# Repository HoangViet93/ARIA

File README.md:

# SRS Studio

Quản lý System / Component Requirements cho automotive — kiểu Codebeamer nhưng
gọn, chạy offline, và **lưu dữ liệu thẳng trong LaTeX** để versioning bằng git.

- Cây item lồng nhau, bảy loại: **Information / Function / Design / DVP /
  Calibration / Interface / Component**
- Mã item bền vững `BCM-0007`, không bao giờ tái sử dụng
- Rich text đầy đủ: bảng, ảnh, link ngoài, link nội bộ tới item, công thức
- Sáu góc nhìn: Tài liệu · Bảng item · **Truy vết dạng sơ đồ** · **UI/UX** ·
  **Component** · LaTeX
- Tín hiệu và biến hiệu chuẩn dạng **enum**: danh sách giá trị, mặc định chọn
  ngay trong danh sách nên không lệch được
- **Sticker ảnh hưởng UI/UX** trên Function/Design, kèm Setting người dùng và
  Cảnh báo — gom thành một bảng để gửi team HMI
- **Component** (ECU/module) là một item riêng, hiển thị bảng gộp và mention
  được bằng `@` (3 tab riêng: Component/Calibration/Interface) — tab Component
  lọc mọi Design nhắc tới nó, trích đúng đoạn văn/bullet/hàng bảng chứa mention
  chứ không phải cả item. ECU gửi/nhận của Interface cũng mention được, kèm
  trường Lớp vật lý (CAN/LIN/Ethernet/Hardwired)
- Tìm kiếm TOC theo **toàn bộ nội dung** (không chỉ tiêu đề/mã), lọc thêm theo
  loại item
- Mỗi lần lưu có thay đổi đều tự chụp một bản vào `.history/`, khôi phục bằng nút **Bản lưu**
- **Git tích hợp sẵn**: mỗi project là một repo từ lúc tạo. Bảng lịch sử bên phải
  (`Ctrl+H`), xem lại bản cũ ở chế độ chỉ đọc, baseline bằng tag, khôi phục cả
  tài liệu hoặc từng item — và **so sánh hai phiên bản ở mức item**, không phải mức dòng
- **Workspace nhiều sách**: một repo git cho cả một chương trình xe (vd.
  `VF9-SRS`), gồm nhiều sách (mỗi sách vẫn là một `data.tex` như trước). Mở
  workspace hiện thanh chuyển sách ở đầu màn hình; bảng Lịch sử chỉ lọc theo
  đúng sách đang mở (`git log -- <sách>/data.tex`), không lẫn sách khác.
  **Xuất Excel** quét Function của mọi sách trong workspace ra một file. Nhánh
  git (tạo/merge trên Gerrit, ngoài app) có thể **checkout** thẳng trong app —
  chuyển cả workspace sang trạng thái của nhánh đó.
- Xuất PDF qua XeLaTeX (tiếng Việt có dấu, mục lục, bookmark)
- Zoom khung tài liệu (`Ctrl` + con lăn), tối đa là mức vừa bề rộng trang
- Chịu được sách dài: 288 trang / 1 150 item vẫn cuộn 60 fps — xem
  `docs/PERFORMANCE.md`
- **aria-sim** (`sim/`): mô phỏng sơ đồ khối kiểu Simulink cho MIL theo yêu
  cầu và desktop calibration — monitor yêu cầu chạy trên cả kết quả mô phỏng
  lẫn log xe, nhận dạng tham số plant từ log, nhập/xuất DCM, nhập thẳng từ
  sách ARIA. Xem `sim/README.md`; chạy `npm run sim`.

Đọc `docs/FEATURES.md` (phân tích + feature requirement), `docs/DESIGN.md`
(thiết kế chi tiết) và `docs/PERFORMANCE.md` (đo và tối ưu hiệu năng).

## Yêu cầu

- Node.js >= 18
- XeLaTeX (chỉ cần khi Xuất/Xem trước PDF) với các gói: `fontspec geometry
  array longtable booktabs tabularx graphicx xcolor colortbl enumitem needspace
  titlesec fancyhdr ulem hyperref tikz`
- Font DejaVu Serif / Sans / Sans Mono

## Chạy

```bash
npm install
npm start
```

Nếu Node hoặc TeX Live nằm trong thư mục home (không cài hệ thống), dùng:

```bash
./run.sh
```

## Đóng gói bản Windows

```bash
npm run dist:win
```

Ra `dist/ARIA-<version>-win-portable/` (và file `.zip` tương ứng) — một
**folder**, không phải file `.exe` đơn — kèm sẵn TeX Live rút gọn
(`resources/texlive-win`) nên máy Windows đích không cần cài TeX Live/MiKTeX
riêng để xuất PDF. Người dùng chỉ cần giải nén rồi bấm đúp `Start-ARIA.bat`.

**Vì sao không đóng gói thành 1 file `.exe`:** đã thử (electron-builder, cả
dạng NSIS lẫn dạng đổi tên `electron.exe` trần) — Windows **Smart App
Control** chặn cứng (không có nút "Run anyway") bất kỳ file `.exe` mới, chưa
ký số, chưa có danh tiếng nào, và **mỗi lần build lại app là ra một file khác
hoàn toàn** (icon/version resource nhúng khác, nội dung `app.asar` khác) nên
không bao giờ "tích lũy" được danh tiếng. `Start-ARIA.bat` là văn bản thuần
(không phải PE binary) và chỉ gọi thẳng `node_modules/electron/dist/electron.exe`
— bản `electron.exe` **gốc, chưa chỉnh sửa gì**, giống hệt bản mà rất nhiều
app Electron khác dùng, nên không phải là "một binary mới lạ" theo cách
Smart App Control đánh giá. Không có cách đóng gói `.exe` đơn nào né được vấn
đề này nếu không mua chứng chỉ code-signing thật hoặc tắt hẳn Smart App
Control trên máy đích (tắt là một chiều, không bật lại được nếu không cài lại
Windows).

`scripts/build-portable-win.js` tự tải riêng một bản Electron Windows-x64 (ép
qua `npm_config_platform=win32 npm_config_arch=x64`, khác với `node_modules`
Linux/macOS bạn đang dùng để phát triển) và chỉ mang theo đúng ba gói npm mà
`main.js`/`lib/` thực sự `require()` lúc chạy (`electron`, `isomorphic-git`,
`exceljs`) — không kèm `esbuild` hay các gói dev khác.

## Kiểm thử

```bash
npm test            # 95 ca: model, checker, diff, git, rich text, biên dịch LaTeX thật
npm run test:ui     # 62 ca trên Electron thật (CRUD, 4 tab, lưu, bản lưu)
npm run test:editor # 59 ca bấm từng nút của editor rồi so LaTeX sinh ra
npm run test:git    # 52 ca cho luồng git: commit, xem bản cũ, so sánh, baseline, khôi phục
npm run test:workspace # 17 ca workspace nhiều sách: chuyển sách, lịch sử lọc theo sách, checkout, xuất Excel
npm run test:all    # tất cả — 285 khẳng định
npm run check       # lint data.tex của các project mẫu
```

## Ba project mẫu

| Project | Nội dung |
|---|---|
| `projects/BCM-Door-Lock` | 10 item, 3 cấp — ví dụ tối giản để xem cấu trúc |
| `projects/EPB-Park-Brake` | 22 item, 4 cấp — Electric Park Brake, dùng hết mọi tính năng: ảnh sơ đồ, 5 bảng, công thức, link nội bộ giữa các item, đủ 5 mức ASIL, và một Function cố ý chưa có Design để tab Truy vết có việc báo. **Có sẵn 15 commit và 2 baseline** (`rev-A`, `rev-B`) trải từ tháng 6 đến tháng 9 để thử bảng Lịch sử |
| `projects/VF9-SRS` | **Workspace 4 sách** (EPB, BCM, ADAS, HVAC) trong 1 repo — ví dụ cho tính năng multi-book. Mỗi sách có lịch sử riêng đã seed sẵn; có thêm nhánh `review/epb-emergency-brake` diverge riêng trên sách EPB để thử **checkout**. Sinh lại bằng `npm run sample:workspace -- --force` |

`projects/BCM-Door-Lock` cố ý **chưa** có git — để thử luồng "Khởi tạo git" một nút.

Lịch sử của EPB dựng bằng `npm run seed-history` (thêm `--force` để dựng lại).
Script giữ nguyên từng byte `data.tex` hiện có, nên chỉnh sửa tay không bị mất.
Ba mốc đáng xem khi so sánh:

| So sánh | Thấy gì |
|---|---|
| `rev-A` → `rev-B` | 11 item mới, 3 chuyển chỗ, ASIL tăng C→D (cảnh báo vàng) |
| "Định nghĩa khung CAN" → "Rút gọn kiểm chứng cho DEB" | bỏ Simulation và Demonstration — **cảnh báo đỏ** |
| "Thêm phanh khẩn cấp" → "Siết ASIL" | ASIL C→D kèm bổ sung Review |

Sinh lại bằng `npm run sample` / `node scripts/make-epb-sample.js`
(ảnh sơ đồ: `npx electron scripts/make-diagram.js`).

## Cấu trúc một project

```
MyProject/
  data.tex        ← TOÀN BỘ dữ liệu. Sửa tay được, git diff có nghĩa.
  images/         ← ảnh đính kèm
  .git/           ← repo chuẩn; git CLI và mọi GUI git đều đọc được
  .gitignore      ← app tạo
  .history/       ← bản lưu tự động trước mỗi lần ghi đè (giữ 30 bản gần nhất, bị gitignore)
  template.tex    ← app ghi đè mỗi lần compile, đừng sửa ở đây
  template.pdf    ← kết quả
```

Muốn đổi cách trình bày PDF: sửa `resources/template.tex` trong mã nguồn app —
một lần, áp dụng cho mọi project.

## Baseline / lịch sử

Git chạy bằng `isomorphic-git` (thuần JavaScript) nên **không cần cài git trên máy**.
Repo sinh ra vẫn hoàn toàn chuẩn — `git log`, `git push`, VS Code, GitKraken đều dùng được.

Baseline = annotated tag. So sánh hai baseline cho ra danh sách **item** thêm/xóa/sửa/chuyển chỗ,
kèm cảnh báo riêng cho thay đổi nhạy cảm về an toàn (ASIL giảm, bớt phương pháp kiểm chứng,
xóa item còn được tham chiếu).

App có thể **checkout** một nhánh có sẵn (nút nhánh trên thanh workspace) —
chuyển cả working tree sang trạng thái nhánh đó, chặn lại nếu còn thay đổi
chưa commit. Tạo/merge nhánh, giải quyết xung đột, push, và mọi thao tác qua
SSH vẫn ngoài phạm vi app — làm trên Gerrit hoặc bằng git CLI, repo là repo thật.

**Giới hạn đã biết:** `\docnextid` là một bộ đếm duy nhất trong file, nên hai nhánh
song song có thể cấp trùng mã item. `validate()` phát hiện được mã trùng sau khi merge.
Xem `docs/GIT-FEATURE.md` §7.1.

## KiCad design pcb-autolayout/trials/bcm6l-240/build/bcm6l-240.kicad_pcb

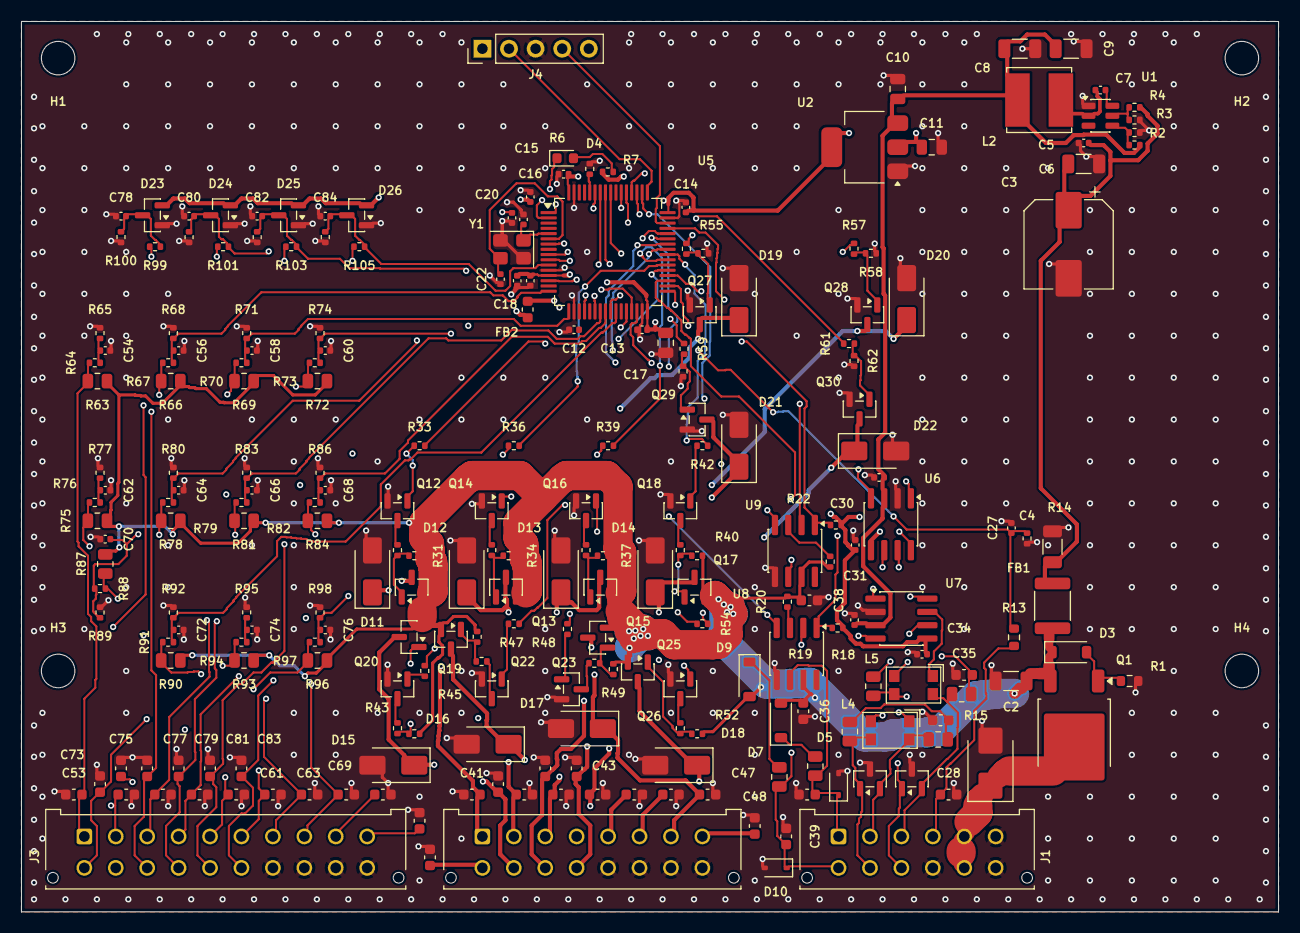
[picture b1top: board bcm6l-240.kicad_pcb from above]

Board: 6 copper layers, 120.0 x 85.0 mm, 239 parts (0 on the bottom side), 134 nets.

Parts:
C2: 100n 50V; C_1206_3216Metric
C3: 47u 35V; CP_Elec_8x10
C4: 4u7 50V; C_1206_3216Metric
C5: 10u 50V; C_1206_3216Metric
C6: 100n 50V; C_0402_1005Metric
C7, C12, C13, C14, C15, C16, C18, C20, C30, C31, C33, C34, C78, C80, C82, C84: 100n; C_0402_1005Metric
C8, C9: 22u 10V; C_1206_3216Metric
C10: 10u; C_0805_2012Metric
C11: 22u; C_0805_2012Metric
C17: 4u7; C_0805_2012Metric
C19: 1u; C_0402_1005Metric
C21, C22: 20p; C_0402_1005Metric
C27, C54, C56, C58, C60, C62, C64, C66, C68, C70, C72, C74, C76: 10n; C_0402_1005Metric
C28, C41, C42, C43, C44, C45, C46, C47, C48, C49, C50, C51, C52, C53, C55, C57, C59, C61, C63, C65, C67, C69, C71, C73, C75, C77, C79, C81, C83: 10n 50V; C_0603_1608Metric
C32, C35: 4n7; C_0603_1608Metric
C36, C38: 100n 50V; C_0603_1608Metric
C37, C39: 220p 50V; C_0603_1608Metric
D1: SMBJ24A; D_SMB
D3: BZT52C10; D_SOD-123
D4: LED; LED_0603_1608Metric
D5, D6: PESD2CAN; SOT-23
D7, D9: BAS21; D_SOD-123
D8, D10: ESD LIN; D_SOD-323
D11, D12, D13, D14, D15, D16, D17, D18: SS14; D_SMA
D19, D20, D21, D22: SMAJ33A; D_SMA
D23, D24, D25, D26: BAT54S; SOT-23
FB1: 600R@100M 3A; L_1812_4532Metric
FB2: 120R@100M; L_0603_1608Metric
H1, H2, H3, H4: M3; MountingHole_3.2mm_M3
J1: MicroFit 2x6; Molex_Micro-Fit_3.0_43045-1212_2x06_P3.00mm_Vertical
J2: MicroFit 2x8; Molex_Micro-Fit_3.0_43045-1612_2x08_P3.00mm_Vertical
J3: MicroFit 2x10; Molex_Micro-Fit_3.0_43045-2012_2x10_P3.00mm_Vertical
J4: SWD; PinHeader_1x05_P2.54mm_Vertical
L2: 10u; L_Bourns_SRN6045TA
L4, L5: CMC 51uH; L_CommonModeChoke_Coilcraft_1812CAN
Q1: SQD40P06 (P-MOS); TO-252-2
Q11, Q13, Q15, Q17, Q19, Q21, Q23, Q25: AO3401A; SOT-23
Q12, Q14, Q16, Q18, Q20, Q22, Q24, Q26: MMBT3904; SOT-23
Q27, Q28, Q29, Q30: 2N7002; SOT-23
R1: 10k; R_0603_1608Metric
R2, R4, R56, R58, R60, R62: 100k; R_0402_1005Metric
R3: 13k7; R_0402_1005Metric
R5: 22k; R_0402_1005Metric
R6, R14, R20, R23, R31, R32, R34, R35, R37, R38, R40, R41, R43, R44, R46, R47, R49, R50, R52, R53, R65, R68, R71, R74, R77, R80, R83, R86, R89, R92, R95, R98, R99, R101, R103, R105: 10k; R_0402_1005Metric
R7, R33, R36, R39, R42, R45, R48, R51, R54: 1k; R_0402_1005Metric
R13: 47k; R_0603_1608Metric
R15, R16, R17, R18: 60R4; R_0805_2012Metric
R19, R22: 4k7; R_0402_1005Metric
R21, R24: 1k; R_0805_2012Metric
R55, R57, R59, R61: 100R; R_0402_1005Metric
R63, R66, R69, R72, R75, R78, R81, R84, R87, R90, R93, R96: 2k2; R_0805_2012Metric
R64, R67, R70, R73, R76, R79, R82, R85, R88, R91, R94, R97: 47k; R_0402_1005Metric
R100, R102, R104, R106: 20k; R_0402_1005Metric
U1: TPS54202; SOT-23-6
U2: AMS1117-3.3; SOT-223-3_TabPin2
U5: STM32F105RBT6; LQFP-64_10x10mm_P0.5mm
U6, U7: TJA1051T/3; SOIC-8_3.9x4.9mm_P1.27mm
U8, U9: TJA1021T/20; SOIC-8_3.9x4.9mm_P1.27mm
Y1: 8MHz; Crystal_SMD_3225-4Pin_3.2x2.5mm

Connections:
+3V3: C11.1, C12.1, C13.1, C14.1, C15.1, C16.1, C17.1, C31.1, C34.1, D23.2, D24.2, D25.2, D26.2, FB2.1, J4.1, R7.1, R19.2, R22.2, U2.2, U5.1, U5.19, U5.32, U5.48, U5.64, U6.5, U7.5
+3V3A: C18.1, C19.1, FB2.2, U5.13
+5V: C8.1, C9.1, C10.1, C30.1, C33.1, L2.2, R2.1, U2.3, U6.3, U7.3
AIN1: C77.1, J3.13, R99.1
AIN1_M: C78.1, D23.3, R99.2, R100.1, U5.8
AIN2: C79.1, J3.14, R101.1
AIN2_M: C80.1, D24.3, R101.2, R102.1, U5.9
AIN3: C81.1, J3.15, R103.1
AIN3_M: C82.1, D25.3, R103.2, R104.1, U5.10
AIN4: C83.1, J3.16, R105.1
AIN4_M: C84.1, D26.3, R105.2, R106.1, U5.11
BOOT0: R6.1, U5.60
BOOT5: C7.1, U1.6
CAN1H: D5.2, J1.2, L4.4, R15.1
CAN1H_T: L4.1, U6.7
CAN1L: D5.1, J1.8, L4.3, R16.1
CAN1L_T: L4.2, U6.6
CAN1_RX: U5.44, U6.4
CAN1_S: U5.56, U6.8
CAN1_SPL: C32.1, R15.2, R16.2
CAN1_TX: U5.45, U6.1
CAN2H: D6.2, J1.3, L5.4, R17.1
CAN2H_T: L5.1, U7.7
CAN2L: D6.1, J1.9, L5.3, R18.1
CAN2L_T: L5.2, U7.6
CAN2_RX: U5.33, U7.4
CAN2_S: U5.57, U7.8
CAN2_SPL: C35.1, R17.2, R18.2
CAN2_TX: U5.34, U7.1
DIN1: C53.1, J3.1, R63.2, R64.1
DIN1_M: C54.1, R64.2, R65.1, U5.15
DIN2: C55.1, J3.2, R66.2, R67.1
DIN2_M: C56.1, R67.2, R68.1, U5.16
DIN3: C57.1, J3.3, R69.2, R70.1
DIN3_M: C58.1, R70.2, R71.1, U5.17
DIN4: C59.1, J3.4, R72.2, R73.1
DIN4_M: C60.1, R73.2, R74.1, U5.20
DIN5: C61.1, J3.5, R75.2, R76.1
DIN5_M: C62.1, R76.2, R77.1, U5.21
DIN6: C63.1, J3.6, R78.2, R79.1
DIN6_M: C64.1, R79.2, R80.1, U5.22
DIN7: C65.1, J3.7, R81.2, R82.1
DIN7_M: C66.1, R82.2, R83.1, U5.23
DIN8: C67.1, J3.8, R84.2, R85.1
DIN8_M: C68.1, R85.2, R86.1, U5.24
DIN9: C69.1, J3.9, R87.2, R88.1
DIN9_M: C70.1, R88.2, R89.1, U5.25
DIN10: C71.1, J3.10, R90.2, R91.1
DIN10_M: C72.1, R91.2, R92.1, U5.26
DIN11: C73.1, J3.11, R93.2, R94.1
DIN11_M: C74.1, R94.2, R95.1, U5.27
DIN12: C75.1, J3.12, R96.2, R97.1
DIN12_M: C76.1, R97.2, R98.1, U5.28
EN5: R4.2, R5.1, U1.5
FB5: R2.2, R3.1, U1.4
GND: C2.2, C3.2, C4.2, C5.2, C6.2, C8.2, C9.2, C10.2, C11.2, C12.2, C13.2, C14.2, C15.2, C16.2, C17.2, C18.2, C19.2, C20.2, C21.2, C22.2, C27.2, C28.2, C30.2, C31.2, C32.2, C33.2, C34.2, C35.2, C36.2, C37.2, C38.2, C39.2, C41.2, C42.2, C43.2, C44.2, C45.2, C46.2, C47.2, C48.2, C49.2, C50.2, C51.2, C52.2, C53.2, C54.2, C55.2, C56.2, C57.2, C58.2, C59.2, C60.2, C61.2, C62.2, C63.2, C64.2, C65.2, C66.2, C67.2, C68.2, C69.2, C70.2, C71.2, C72.2, C73.2, C74.2, C75.2, C76.2, C77.2, C78.2, C79.2, C80.2, C81.2, C82.2, C83.2, C84.2, D1.2, D5.3, D6.3, D8.2, D10.2, D11.2, D12.2, D13.2, D14.2, D15.2, D16.2, D17.2, D18.2, D19.2, D20.2, D21.2, D22.2, D23.1, D24.1, D25.1, D26.1, J1.6, J1.10, J1.12, J2.13, J2.14, J2.15, J2.16, J3.17, J3.18, J3.19, J3.20, J4.3, Q12.2, Q14.2, Q16.2, Q18.2, Q20.2, Q22.2, Q24.2, Q26.2, Q27.2, Q28.2, Q29.2, Q30.2, R1.2, R3.2, R5.2, R6.2, R14.2, R56.2, R58.2, R60.2, R62.2, R65.2, R68.2, R71.2, R74.2, R77.2, R80.2, R83.2, R86.2, R89.2, R92.2, R95.2, R98.2, R100.2, R102.2, R104.2, R106.2, U1.1, U2.1, U5.12, U5.18, U5.31, U5.47, U5.63, U6.2, U7.2, U8.5, U9.5, Y1.2, Y1.4
KL15: C28.1, J1.4, R13.1
KL15_M: C27.1, R13.2, R14.1, U5.14
LED_A: D4.2, R7.2
LED_K: D4.1, U5.2
LIN1: C37.1, D8.1, J1.1, R21.2, U8.6
LIN1_PU: D7.1, R21.1
LIN1_RX: R19.1, U5.30, U8.1
LIN1_SLP: U5.35, U8.2
LIN1_TX: U5.29, U8.4
LIN1_WAKE: R20.1, U8.3
LIN2: C39.1, D10.1, J1.7, R24.2, U9.6
LIN2_PU: D9.1, R24.1
LIN2_RX: R22.1, U5.59, U9.1
LIN2_SLP: U5.36, U9.2
LIN2_TX: U5.58, U9.4
LIN2_WAKE: R23.1, U9.3
LS1: C49.1, D19.1, J2.9, Q27.3
LS1_G: Q27.1, R55.2, R56.1
LS1_M: R55.1, U5.51
LS2: C50.1, D20.1, J2.10, Q28.3
LS2_G: Q28.1, R57.2, R58.1
LS2_M: R57.1, U5.52
LS3: C51.1, D21.1, J2.11, Q29.3
LS3_G: Q29.1, R59.2, R60.1
LS3_M: R59.1, U5.53
LS4: C52.1, D22.1, J2.12, Q30.3
LS4_G: Q30.1, R61.2, R62.1
LS4_M: R61.1, U5.54
NRST: C20.1, J4.5, U5.7
OSC_IN: C21.1, U5.5, Y1.1
OSC_OUT: C22.1, U5.6, Y1.3
OUT1: C41.1, D11.1, J2.1, Q11.3
OUT1_B: Q12.1, R33.2
OUT1_C: Q12.3, R32.2
OUT1_G: Q11.1, R31.2, R32.1
OUT1_M: R33.1, U5.37
OUT2: C42.1, D12.1, J2.2, Q13.3
OUT2_B: Q14.1, R36.2
OUT2_C: Q14.3, R35.2
OUT2_G: Q13.1, R34.2, R35.1
OUT2_M: R36.1, U5.38
OUT3: C43.1, D13.1, J2.3, Q15.3
OUT3_B: Q16.1, R39.2
OUT3_C: Q16.3, R38.2
OUT3_G: Q15.1, R37.2, R38.1
OUT3_M: R39.1, U5.39
OUT4: C44.1, D14.1, J2.4, Q17.3
OUT4_B: Q18.1, R42.2
OUT4_C: Q18.3, R41.2
OUT4_G: Q17.1, R40.2, R41.1
OUT4_M: R42.1, U5.40
OUT5: C45.1, D15.1, J2.5, Q19.3
OUT5_B: Q20.1, R45.2
OUT5_C: Q20.3, R44.2
OUT5_G: Q19.1, R43.2, R44.1
OUT5_M: R45.1, U5.41
OUT6: C46.1, D16.1, J2.6, Q21.3
OUT6_B: Q22.1, R48.2
OUT6_C: Q22.3, R47.2
OUT6_G: Q21.1, R46.2, R47.1
OUT6_M: R48.1, U5.42
OUT7: C47.1, D17.1, J2.7, Q23.3
OUT7_B: Q24.1, R51.2
OUT7_C: Q24.3, R50.2
OUT7_G: Q23.1, R49.2, R50.1
OUT7_M: R51.1, U5.43
OUT8: C48.1, D18.1, J2.8, Q25.3
OUT8_B: Q26.1, R54.2
OUT8_C: Q26.3, R53.2
OUT8_G: Q25.1, R52.2, R53.1
OUT8_M: R54.1, U5.50
Q1_G: D3.2, Q1.1, R1.1
SW5: C7.2, L2.1, U1.2
SWCLK: J4.2, U5.49
SWDIO: J4.4, U5.46
VBAT_F: C3.1, C4.1, C5.1, C6.1, FB1.2, R4.1, U1.3
VBAT_IN: D1.1, J1.5, J1.11, Q1.2
VBAT_P: C2.1, C36.1, C38.1, D3.1, D7.2, D9.2, FB1.1, Q1.3, Q11.2, Q13.2, Q15.2, Q17.2, Q19.2, Q21.2, Q23.2, Q25.2, R20.2, R23.2, R31.1, R34.1, R37.1, R40.1, R43.1, R46.1, R49.1, R52.1, R63.1, R66.1, R69.1, R72.1, R75.1, R78.1, R81.1, R84.1, R87.1, R90.1, R93.1, R96.1, U8.7, U9.7

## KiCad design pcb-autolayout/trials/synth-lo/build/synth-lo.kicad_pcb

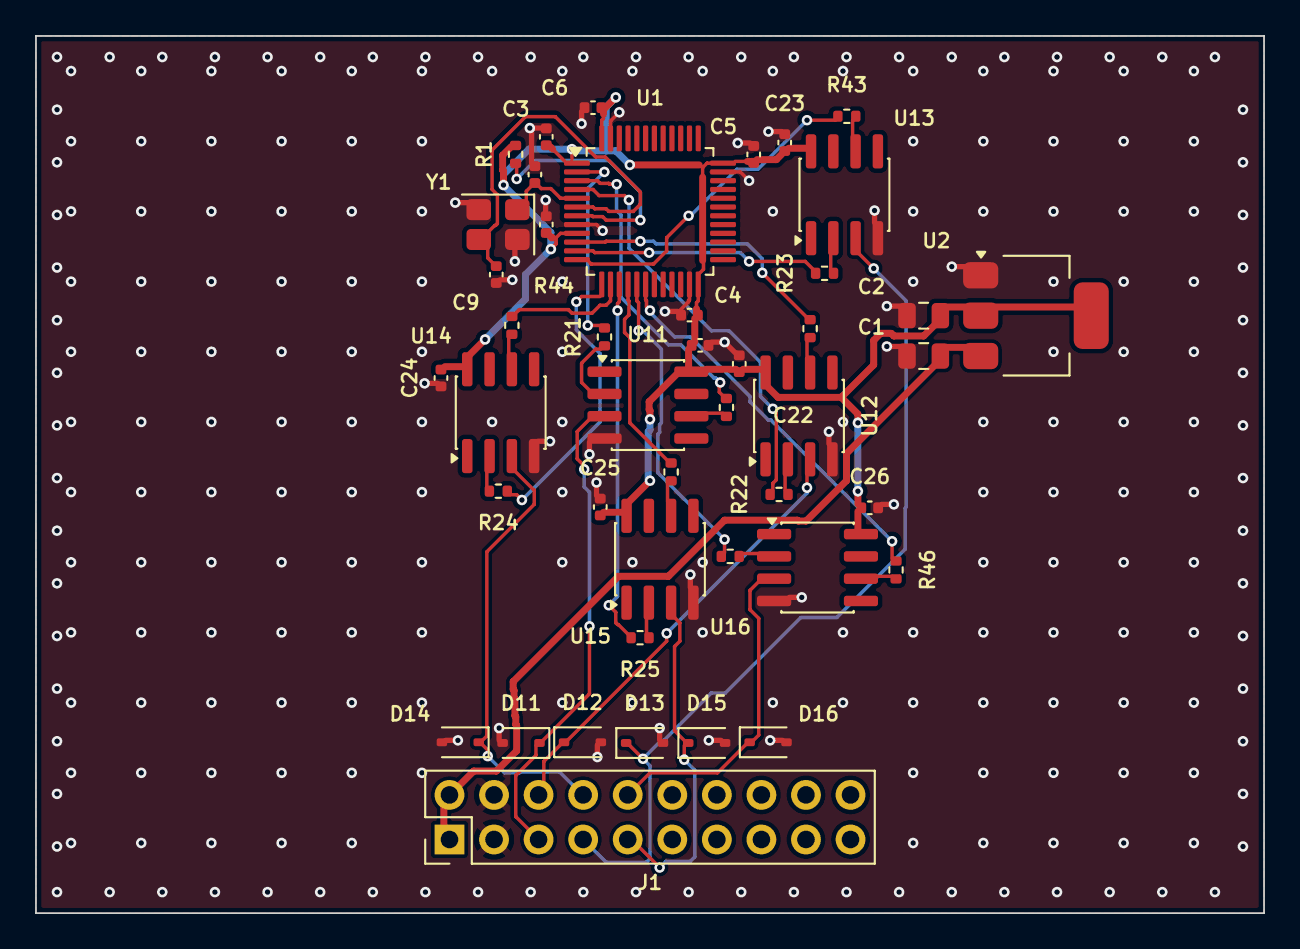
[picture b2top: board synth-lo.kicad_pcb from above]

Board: 4 copper layers, 70.0 x 50.0 mm, 44 parts (0 on the bottom side), 36 nets.

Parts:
C1, C2: 10u; C_0805_2012Metric
C3, C4, C5, C6, C21, C22, C23, C24, C25, C26: 100n; C_0402_1005Metric
C7: 1u; C_0402_1005Metric
C8, C9: 12p; C_0402_1005Metric
D11, D12, D13, D14, D15, D16: ESD; D_SOD-323
J1: CONN; PinHeader_2x10_P2.54mm_Vertical
R1: 10k; R_0402_1005Metric
R21, R22, R23, R24, R25, R26: 33R; R_0402_1005Metric
R41, R42, R43, R44, R45, R46: 1k; R_0402_1005Metric
U1: MCU; LQFP-48_7x7mm_P0.5mm
U2: LDO; SOT-223-3_TabPin2
U11, U12, U13, U14, U15, U16: BUF; SOIC-8_3.9x4.9mm_P1.27mm
Y1: 8MHz; Crystal_SMD_3225-4Pin_3.2x2.5mm

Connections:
+3V3: C2.1, C3.1, C4.1, C5.1, C6.1, C7.1, C21.1, C22.1, C23.1, C24.1, C25.1, C26.1, R1.2, U1.1, U1.9, U1.24, U1.36, U1.48, U2.2, U11.8, U12.8, U13.8, U14.8, U15.8, U16.8
GND: C1.2, C2.2, C3.2, C4.2, C5.2, C6.2, C7.2, C8.2, C9.2, C21.2, C22.2, C23.2, C24.2, C25.2, C26.2, D11.2, D12.2, D13.2, D14.2, D15.2, D16.2, J1.3, J1.4, U1.8, U1.23, U1.35, U1.47, U2.1, U11.4, U12.4, U13.4, U14.4, U15.4, U16.4, Y1.2, Y1.4
NRST: R1.1, U1.7
OSC_IN: C8.1, U1.5, Y1.1
OSC_OUT: C9.1, U1.6, Y1.3
S1_A: R21.1, U1.2
S1_B: R41.2, U1.3
S1_FB: R41.1, U11.6
S1_IN: R21.2, U11.2
S1_OUT: D11.1, J1.5, U11.3
S2_A: R22.1, U1.4
S2_B: R42.2, U1.10
S2_FB: R42.1, U12.6
S2_IN: R22.2, U12.2
S2_OUT: D12.1, J1.6, U12.3
S3_A: R23.1, U1.11
S3_B: R43.2, U1.12
S3_FB: R43.1, U13.6
S3_IN: R23.2, U13.2
S3_OUT: D13.1, J1.7, U13.3
S4_A: R24.1, U1.13
S4_B: R44.2, U1.14
S4_FB: R44.1, U14.6
S4_IN: R24.2, U14.2
S4_OUT: D14.1, J1.8, U14.3
S5_A: R25.1, U1.15
S5_B: R45.2, U1.16
S5_FB: R45.1, U15.6
S5_IN: R25.2, U15.2
S5_OUT: D15.1, J1.9, U15.3
S6_A: R26.1, U1.17
S6_B: R46.2, U1.18
S6_FB: R46.1, U16.6
S6_IN: R26.2, U16.2
S6_OUT: D16.1, J1.10, U16.3
VIN: C1.1, J1.1, J1.2, U2.3

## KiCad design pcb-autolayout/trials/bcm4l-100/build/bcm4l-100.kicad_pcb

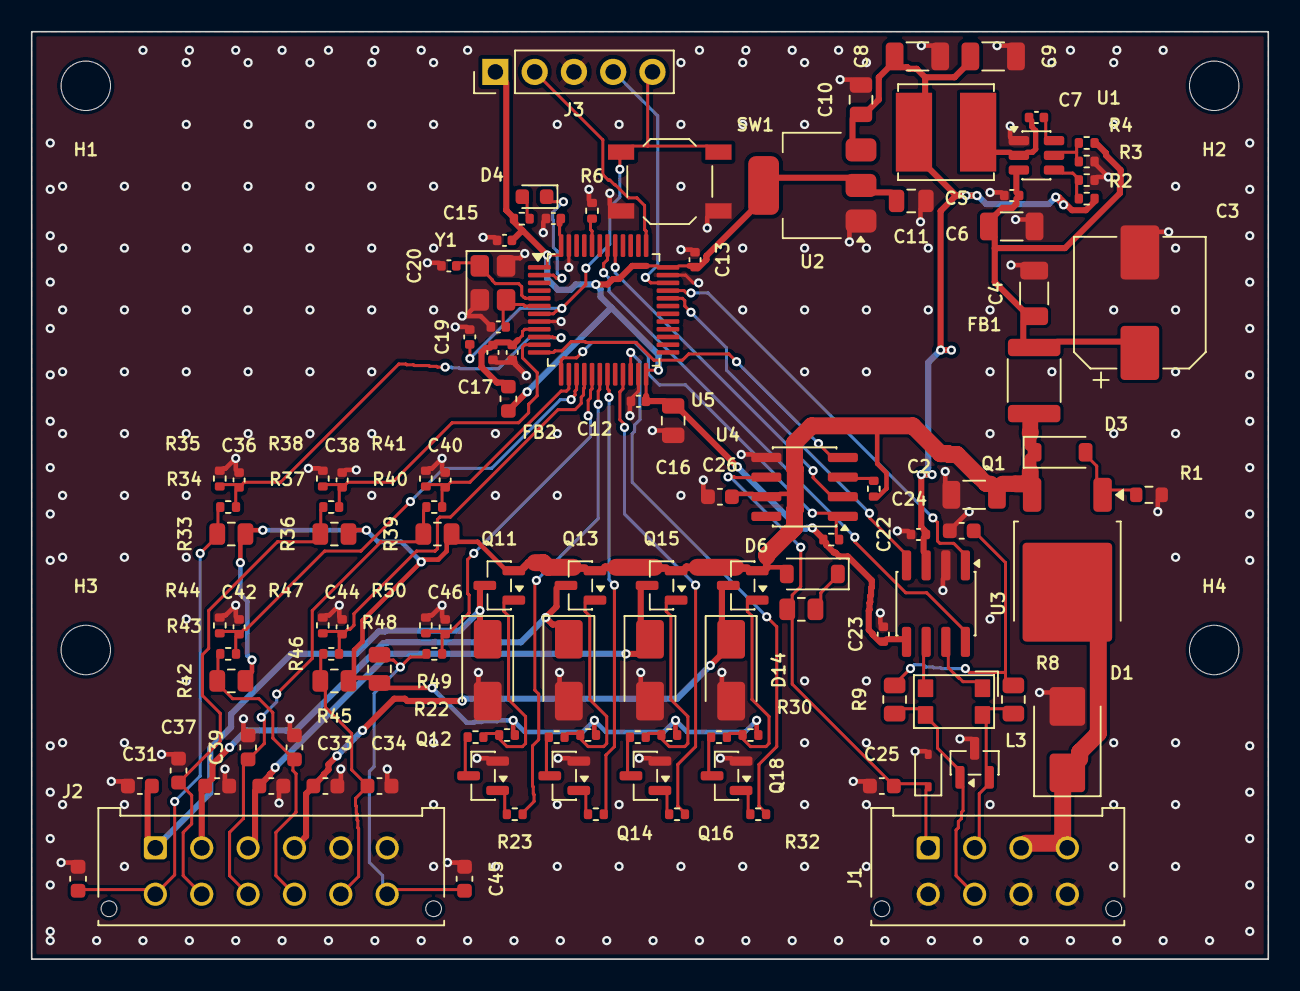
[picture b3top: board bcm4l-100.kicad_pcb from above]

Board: 4 copper layers, 80.0 x 60.0 mm, 120 parts (0 on the bottom side), 66 nets.

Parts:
C2: 100n 50V; C_1206_3216Metric
C3: 47u 35V; CP_Elec_8x10
C4: 4u7 50V; C_1206_3216Metric
C5: 10u 50V; C_1206_3216Metric
C6: 100n 50V; C_0402_1005Metric
C7, C12, C13, C14, C15, C17, C19, C22, C23: 100n; C_0402_1005Metric
C8, C9: 22u 10V; C_1206_3216Metric
C10: 10u; C_0805_2012Metric
C11: 22u; C_0805_2012Metric
C16: 4u7; C_0805_2012Metric
C18: 1u; C_0402_1005Metric
C20, C21: 20p; C_0402_1005Metric
C24: 4n7; C_0603_1608Metric
C25: 1n 50V; C_0603_1608Metric
C26: 100n 50V; C_0603_1608Metric
C31, C32, C33, C34, C35, C37, C39, C41, C43, C45: 10n 50V; C_0603_1608Metric
C36, C38, C40, C42, C44, C46: 10n; C_0402_1005Metric
D1: SMBJ24A; D_SMB
D3: BZT52C10; D_SOD-123
D4: LED; LED_0603_1608Metric
D5: PESD2CAN; SOT-23
D6: BAS21; D_SOD-123
D7: ESD LIN; D_SOD-323
D11, D12, D13, D14: SS14; D_SMA
FB1: 600R@100M 3A; L_1812_4532Metric
FB2: 120R@100M; L_0603_1608Metric
H1, H2, H3, H4: M3; MountingHole_3.2mm_M3
J1: MicroFit 2x4; Molex_Micro-Fit_3.0_43045-0812_2x04_P3.00mm_Vertical
J2: MicroFit 2x6; Molex_Micro-Fit_3.0_43045-1212_2x06_P3.00mm_Vertical
J3: SWD; PinHeader_1x05_P2.54mm_Vertical
L2: 10u; L_Bourns_SRN6045TA
L3: CMC 51uH; L_CommonModeChoke_Coilcraft_1812CAN
Q1: SQD40P06 (P-MOS); TO-252-2
Q11, Q13, Q15, Q17: AO3401A; SOT-23
Q12, Q14, Q16, Q18: MMBT3904; SOT-23
R1: 10k; R_0603_1608Metric
R2, R4: 100k; R_0402_1005Metric
R3: 13k7; R_0402_1005Metric
R5: 22k; R_0402_1005Metric
R6, R12, R21, R22, R24, R25, R27, R28, R30, R31, R35, R38, R41, R44, R47, R50: 10k; R_0402_1005Metric
R7, R23, R26, R29, R32: 1k; R_0402_1005Metric
R8, R9: 60R4; R_0805_2012Metric
R10: 1k; R_0805_2012Metric
R11: 4k7; R_0402_1005Metric
R33, R36, R39, R42, R45, R48: 2k2; R_0805_2012Metric
R34, R37, R40, R43, R46, R49: 47k; R_0402_1005Metric
SW1: RESET; SW_SPST_TL3342
U1: TPS54202; SOT-23-6
U2: AMS1117-3.3; SOT-223-3_TabPin2
U3: TJA1051T/3; SOIC-8_3.9x4.9mm_P1.27mm
U4: TJA1021T/20; SOIC-8_3.9x4.9mm_P1.27mm
U5: STM32F103C8T6; LQFP-48_7x7mm_P0.5mm
Y1: 8MHz; Crystal_SMD_3225-4Pin_3.2x2.5mm

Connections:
+3V3: C11.1, C12.1, C13.1, C14.1, C15.1, C16.1, C23.1, FB2.1, J3.1, R7.1, R11.2, U2.2, U3.5, U5.1, U5.24, U5.36, U5.48
+3V3A: C17.1, C18.1, FB2.2, U5.9
+5V: C8.1, C9.1, C10.1, C22.1, L2.2, R2.1, U2.3, U3.3
BOOT0: R6.1, U5.44
BOOT5: C7.1, U1.6
CANH: D5.2, J1.2, L3.4, R8.1
CANH_T: L3.1, U3.7
CANL: D5.1, J1.6, L3.3, R9.1
CANL_T: L3.2, U3.6
CAN_RX: U3.4, U5.32
CAN_S: U3.8, U5.42
CAN_SPL: C24.1, R8.2, R9.2
CAN_TX: U3.1, U5.33
EN5: R4.2, R5.1, U1.5
FB5: R2.2, R3.1, U1.4
GND: C2.2, C3.2, C4.2, C5.2, C6.2, C8.2, C9.2, C10.2, C11.2, C12.2, C13.2, C14.2, C15.2, C16.2, C17.2, C18.2, C19.2, C20.2, C21.2, C22.2, C23.2, C24.2, C25.2, C26.2, C31.2, C32.2, C33.2, C34.2, C35.2, C36.2, C37.2, C38.2, C39.2, C40.2, C41.2, C42.2, C43.2, C44.2, C45.2, C46.2, D1.2, D5.3, D7.2, D11.2, D12.2, D13.2, D14.2, J1.5, J1.7, J1.8, J2.5, J2.6, J3.3, Q12.2, Q14.2, Q16.2, Q18.2, R1.2, R3.2, R5.2, R6.2, R35.2, R38.2, R41.2, R44.2, R47.2, R50.2, SW1.2, U1.1, U2.1, U3.2, U4.5, U5.8, U5.23, U5.35, U5.47, Y1.2, Y1.4
IN1: C35.1, J2.7, R33.2, R34.1
IN1_M: C36.1, R34.2, R35.1, U5.10
IN2: C37.1, J2.8, R36.2, R37.1
IN2_M: C38.1, R37.2, R38.1, U5.11
IN3: C39.1, J2.9, R39.2, R40.1
IN3_M: C40.1, R40.2, R41.1, U5.14
IN4: C41.1, J2.10, R42.2, R43.1
IN4_M: C42.1, R43.2, R44.1, U5.15
IN5: C43.1, J2.11, R45.2, R46.1
IN5_M: C44.1, R46.2, R47.1, U5.16
IN6: C45.1, J2.12, R48.2, R49.1
IN6_M: C46.1, R49.2, R50.1, U5.17
LED_A: D4.2, R7.2
LED_K: D4.1, U5.2
LIN: C25.1, D7.1, J1.1, R10.2, U4.6
LIN_PU: D6.1, R10.1
LIN_RX: R11.1, U4.1, U5.13
LIN_SLP: U4.2, U5.41
LIN_TX: U4.4, U5.12
LIN_WAKE: R12.1, U4.3
NRST: C19.1, J3.5, SW1.1, U5.7
OSC_IN: C20.1, U5.5, Y1.1
OSC_OUT: C21.1, U5.6, Y1.3
OUT1: C31.1, D11.1, J2.1, Q11.3
OUT1_B: Q12.1, R23.2
OUT1_C: Q12.3, R22.2
OUT1_G: Q11.1, R21.2, R22.1
OUT1_M: R23.1, U5.18
OUT2: C32.1, D12.1, J2.2, Q13.3
OUT2_B: Q14.1, R26.2
OUT2_C: Q14.3, R25.2
OUT2_G: Q13.1, R24.2, R25.1
OUT2_M: R26.1, U5.19
OUT3: C33.1, D13.1, J2.3, Q15.3
OUT3_B: Q16.1, R29.2
OUT3_C: Q16.3, R28.2
OUT3_G: Q15.1, R27.2, R28.1
OUT3_M: R29.1, U5.21
OUT4: C34.1, D14.1, J2.4, Q17.3
OUT4_B: Q18.1, R32.2
OUT4_C: Q18.3, R31.2
OUT4_G: Q17.1, R30.2, R31.1
OUT4_M: R32.1, U5.22
Q1_G: D3.2, Q1.1, R1.1
SW5: C7.2, L2.1, U1.2
SWCLK: J3.2, U5.37
SWDIO: J3.4, U5.34
VBAT_F: C3.1, C4.1, C5.1, C6.1, FB1.2, R4.1, U1.3
VBAT_IN: D1.1, J1.3, J1.4, Q1.2
VBAT_P: C2.1, C26.1, D3.1, D6.2, FB1.1, Q1.3, Q11.2, Q13.2, Q15.2, Q17.2, R12.2, R21.1, R24.1, R27.1, R30.1, R33.1, R36.1, R39.1, R42.1, R45.1, R48.1, U4.7
